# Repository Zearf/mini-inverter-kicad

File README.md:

# Mini Inverter PCB | My First KiCad Project

A two-layer PCB design exploring a **12V DC-to-AC inverter** using an IR2153 gate driver, two IRLZ24 MOSFETs, and an external transformer. The intended step-up stage targets approximately **240V AC**, but the output has **not been verified**.

This is my first KiCad project, created to practice schematic capture, footprint selection, component placement, PCB routing, and manufacturing-file export.

*Top-view visualization generated from the exported Gerber layers. This is a design preview, not a photograph or a finished 3D rendering.*

## Project Overview

| Specification | Design |
| --- | --- |
| EDA software | KiCad 10 |
| PCB layers | 2 (front and back copper) |
| Board dimensions | Approximately 55.2 × 32.2 mm |
| Board thickness setting | 1.6 mm |
| Input | Nominal 12V DC |
| Intended output | Approximately 240V AC via an external transformer; **unverified** |
| Current stage | PCB design and Gerber export; fabrication/testing not documented |

## Circuit Design

The design explores converting a low-voltage DC supply into an alternating signal that can be applied to a step-up transformer. The **IR2153** is used as a self-oscillating MOSFET driver, while **Q1 and Q2 (IRLZ24)** are the switching devices. The schematic also includes timing/passive components, a potentiometer, an indicator LED, and terminal blocks for external connections.

### Main Components

| Reference | Component | Role in design |
| --- | --- | --- |
| U1 | IR2153 | Self-oscillating gate-driver IC |
| Q1, Q2 | IRLZ24 | N-channel switching MOSFETs |
| T1 | 240V / 12-0-12V transformer (external) | Intended voltage-conversion stage, connected through a terminal block |
| RV1 | 10 kΩ potentiometer | Adjustable element in the circuit |
| BT1 | 12V supply connection | Input terminal block |
| D1 | 1N4007 | Diode |
| D2 | LED | Indicator |
| R1–R6, C1–C4 | Resistors and capacitors | Supporting driver, timing, and filtering circuitry |

## PCB Layout and Routing

The board uses through-hole components and a two-layer copper layout. Its compact footprint was an opportunity to practice component placement, trace routing, copper pours, and silkscreen labeling.

*Copper-layer visualization derived from the Gerber files; the layers are overlaid for illustration.*

## Project Status

- [x] Create schematic and select component footprints
- [x] Design and route the PCB
- [x] Export Gerber and drill files
- [ ] Document electrical-rule and design-rule check results
- [ ] Review the design for high-voltage safety and component ratings
- [ ] Fabricate and assemble the PCB
- [ ] Test the circuit and record measured output

### Items to Review Before Fabrication

- **D3 is an LED symbol assigned to a two-pin terminal-block footprint.** If it represents an output connector, update the schematic symbol so the documentation matches the physical design.
- Verify the **transformer wiring, terminal-block voltage ratings, insulation, creepage/clearance distances, and protection circuitry**. The present files do not establish that the board is safe to produce or energize at the intended high voltage.
- Record and resolve KiCad **ERC/DRC findings** and independently check circuit operation before manufacturing.

 **Safety:** This is an educational, unvalidated design that targets potentially lethal voltages. It should not be connected to mains wiring or energized at high voltage without a qualified design and safety review.

## What I Learned

This project gave me hands-on experience with the workflow from a schematic to a routed PCB, including assigning footprints, organizing components on a compact board, working with two copper layers, and exporting manufacturing files. The next step is validating the electrical design and documenting test results before considering fabrication.

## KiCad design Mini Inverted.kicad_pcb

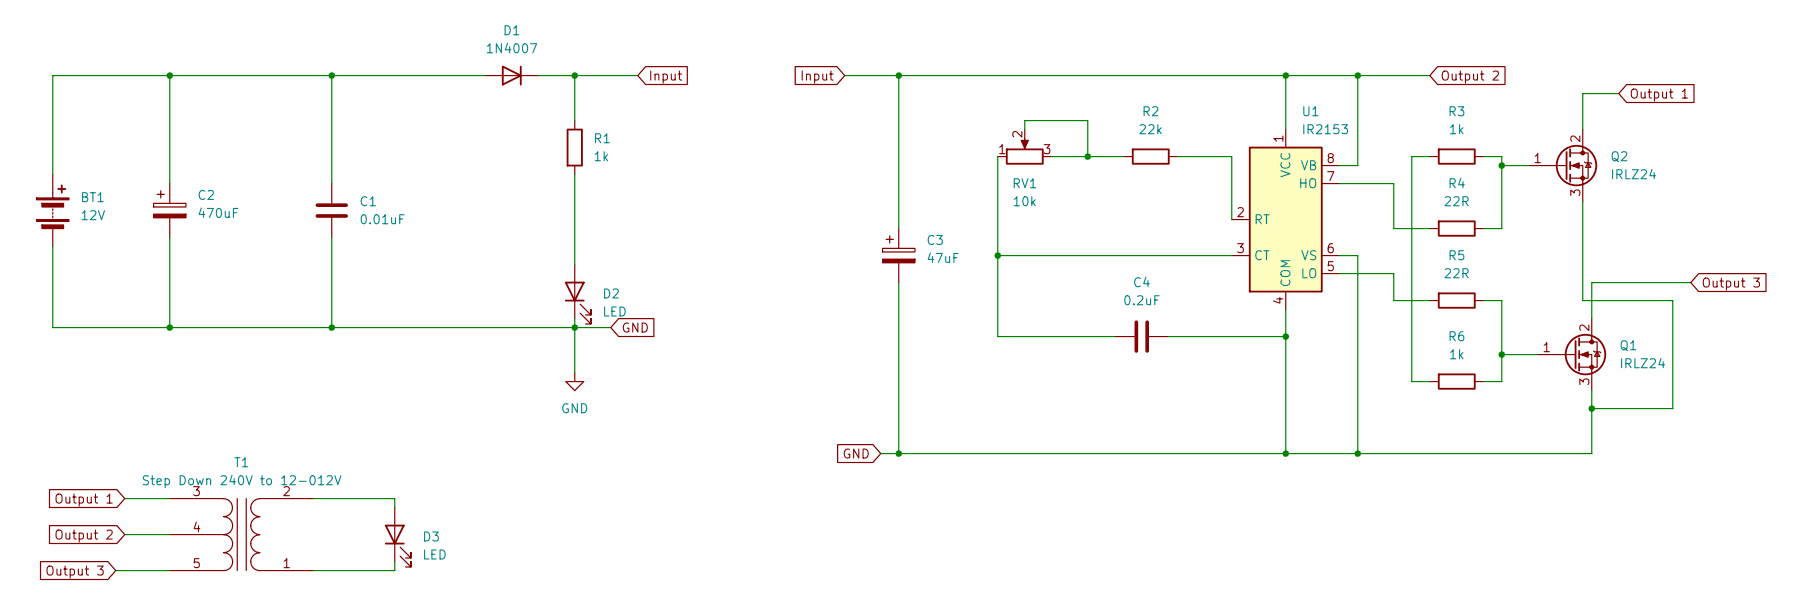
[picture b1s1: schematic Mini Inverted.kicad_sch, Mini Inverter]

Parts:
BT1: 12V; TerminalBlock_Xinya_XY308-2.54-2P_1x02_P2.54mm_Horizontal
C1: 0.01uF; C_Disc_D3.0mm_W1.6mm_P2.50mm
C2: 470uF; CP_Radial_D6.3mm_P2.50mm
C3: 47uF; CP_Radial_D5.0mm_P2.50mm
C4: 0.2uF; C_Disc_D3.0mm_W2.0mm_P2.50mm
D1: 1N4007; D_DO-41_SOD81_P10.16mm_Horizontal
D2: LED; LED_D5.0mm
D3: LED; TerminalBlock_Xinya_XY308-2.54-2P_1x02_P2.54mm_Horizontal
Q1, Q2: IRLZ24; TO-220-3_Vertical
R1, R3, R6: 1k; R_Axial_DIN0204_L3.6mm_D1.6mm_P5.08mm_Horizontal
R2: 22k; R_Axial_DIN0204_L3.6mm_D1.6mm_P5.08mm_Horizontal
R4, R5: 22R; R_Axial_DIN0204_L3.6mm_D1.6mm_P5.08mm_Horizontal
RV1: 10k; Potentiometer_ACP_CA6-H2,5_Horizontal
T1: Step Down 240V to 12-012V; TerminalBlock_Xinya_XY308-2.54-5P_1x05_P2.54mm_Horizontal
U1: IR2153; DIP-8_W7.62mm

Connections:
GND: BT1.2 (-), C1.2, C2.2, C3.2, C4.1, D2.1 (K), Q1.3 (S), Q2.3 (S), U1.4 (COM), U1.6 (VS)
Input: C3.1, D1.1 (K), R1.1, T1.4 (SC), U1.1 (VCC), U1.8 (VB)
unnamed: BT1.1 (+), C1.1, C2.1, D1.2 (A)
unnamed: D2.2 (A), R1.2
unnamed: D3.2 (A), T1.2 (AB)
unnamed: D3.1 (K), T1.1 (AA)
unnamed: Q1.1 (G), R5.1, R6.1
unnamed: Q2.1 (G), R3.1, R4.1
unnamed: R2.2, RV1.2, RV1.3
unnamed: R3.2, R6.2
unnamed: C4.2, RV1.1, U1.3 (CT)
unnamed: R4.2, U1.7 (HO)
unnamed: R5.2, U1.5 (LO)
unnamed: R2.1, U1.2 (RT)
Output 1: Q2.2 (D), T1.3 (SA)
Output 3: Q1.2 (D), T1.5 (SB)

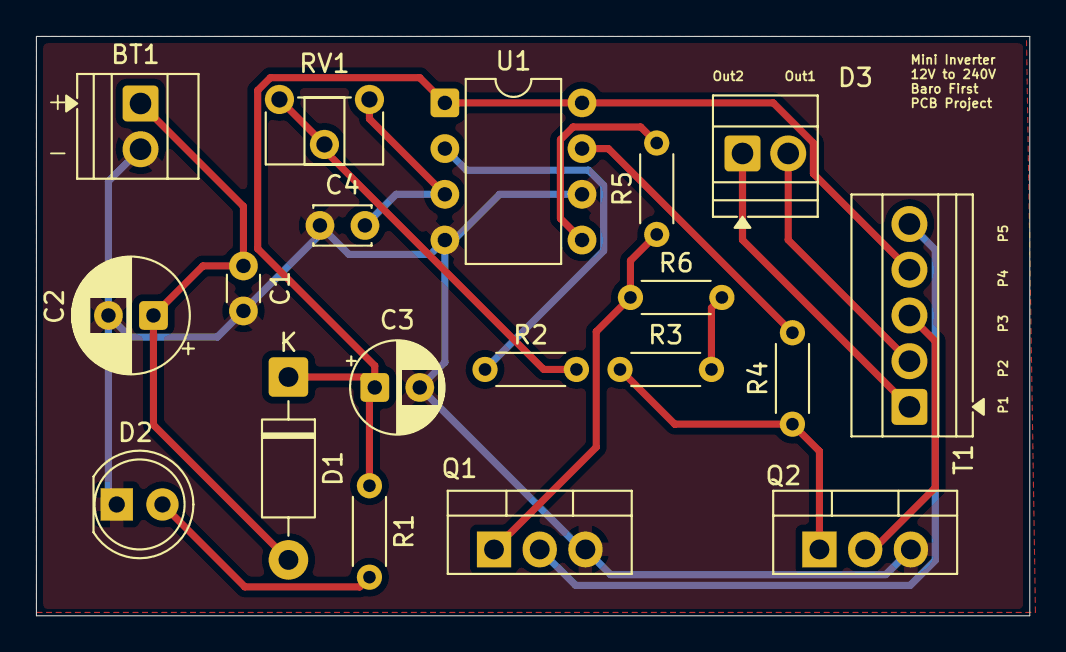
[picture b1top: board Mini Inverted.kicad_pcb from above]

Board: 2 copper layers, 55.2 x 32.2 mm, 19 parts (0 on the bottom side), 16 nets.
